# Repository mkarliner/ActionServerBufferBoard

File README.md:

This is a design for a board to buffer the outputs of a Raspberr Pi so that it can drive 5V devices which use up to 500ma. The buffer chips are ULN2003's which are Darlington pair arrays with open collector outputs. This means that they form low side switches. There are many articles on Google for using ULN2003's so I won't detail wiring here. The silkscreen is marked for the connections for the Camerabotics Lensmaster ActionServer to make it easier to wire up.

PLEASE NOTE: This is a first version of this design. I'm working on a second revision with more/easier connections and push/pull outputs. However, you are welcome to use this if you find it useful.

I've included pictures of the assembled board and my initial installation. The installation has three relay outputs and three 240V solid state relays. (The relay board has 8 relays of which one three are used)

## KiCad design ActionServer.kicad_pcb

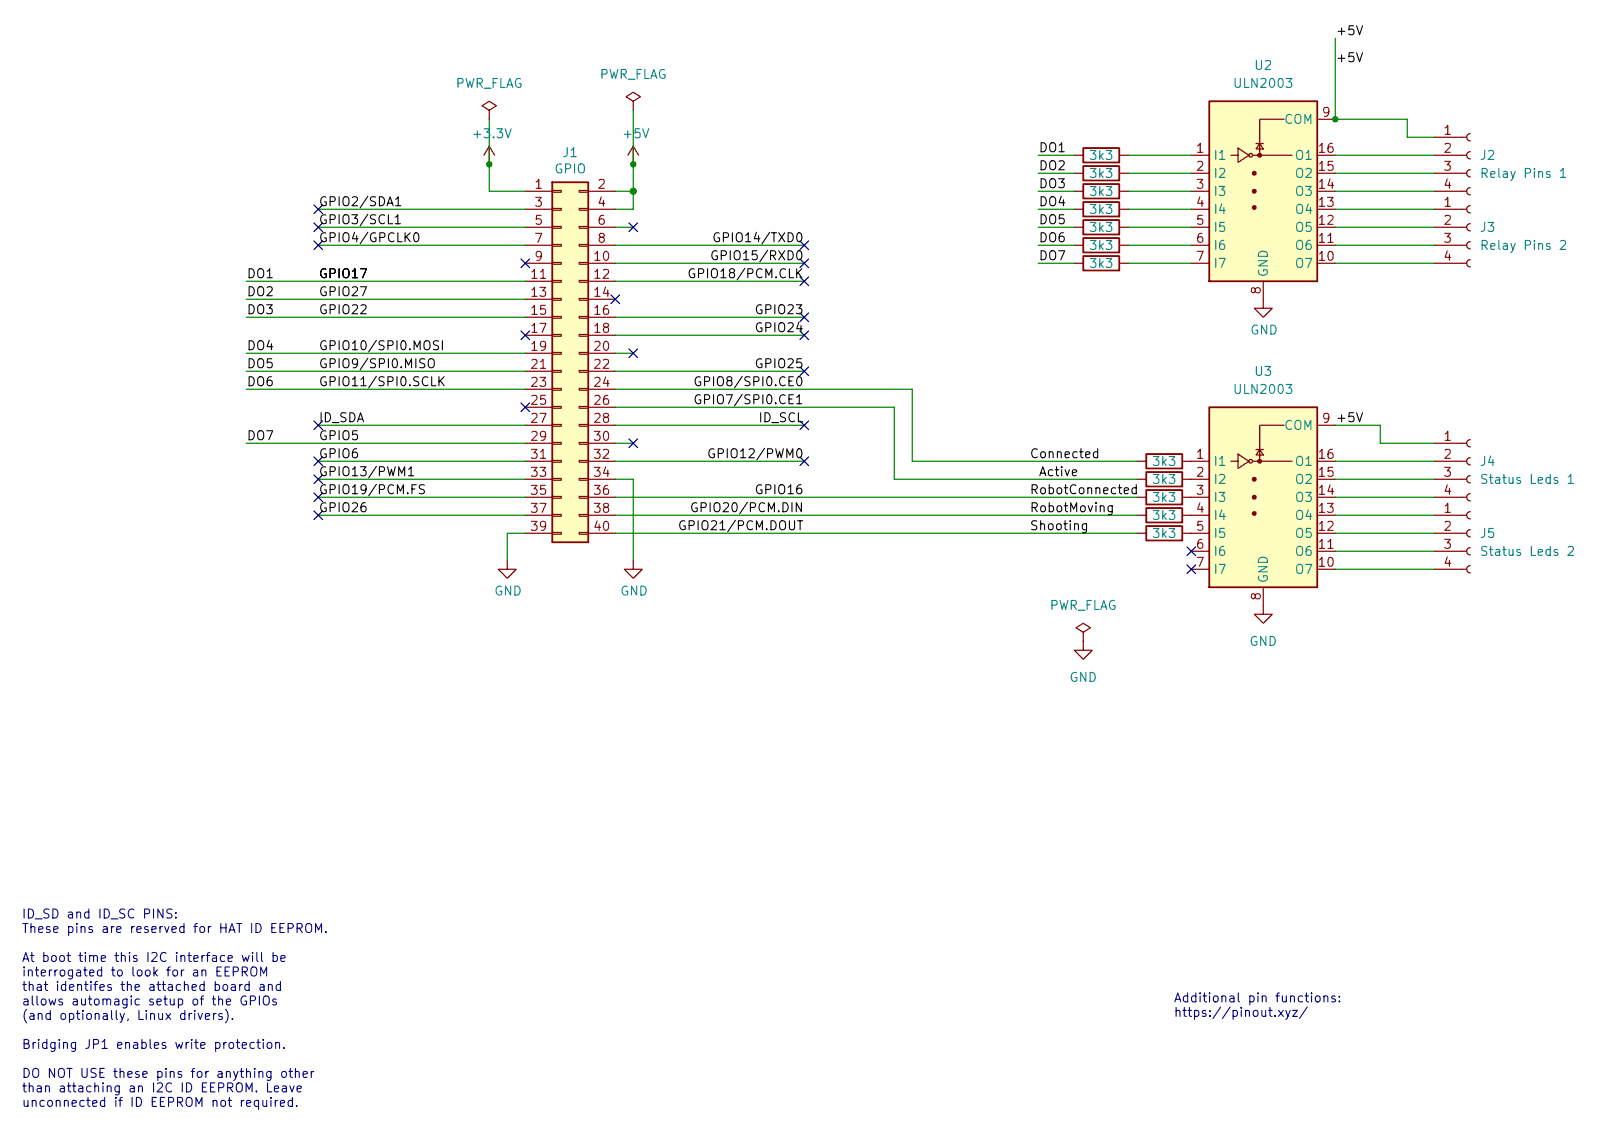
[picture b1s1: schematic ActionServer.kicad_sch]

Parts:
J1: GPIO; PinSocket_2x20_P2.54mm_Vertical
J2: Relay Pins 1; PinHeader_1x04_P2.54mm_Vertical
J3: Relay Pins 2; PinHeader_1x04_P2.54mm_Vertical
J4: Status Leds 1; PinHeader_1x04_P2.54mm_Vertical
J5: Status Leds 2; PinHeader_1x04_P2.54mm_Vertical
R3, R4, R5, R6, R7, R8, R9, R10, R11, R12, R13, R14: 3k3; R_0805_2012Metric
U2, U3: ULN2003; SOIC-16_3.9x9.9mm_P1.27mm

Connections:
+3.3V: J1.1
+5V: J1.2, J1.4, J2.1, J4.1, U2.9 (COM), U3.9 (COM)
/Active: J1.26, R11.1
/Connected: J1.24, R10.1
/DO1: J1.11, R3.1
/DO2: J1.13, R4.1
/DO3: J1.15, R5.1
/DO4: J1.19, R6.1
/DO5: J1.21, R7.1
/DO6: J1.23, R8.1
/DO7: J1.29, R9.1
/GPIO2/SDA1: J1.3
/GPIO3/SCL1: J1.5
/GPIO4/GPCLK0: J1.7
/GPIO6: J1.31
/GPIO12/PWM0: J1.32
/GPIO13/PWM1: J1.33
/GPIO14/TXD0: J1.8
/GPIO15/RXD0: J1.10
/GPIO16: J1.36, R12.1
/GPIO18/PCM.CLK: J1.12
/GPIO19/PCM.FS: J1.35
/GPIO20/PCM.DIN: J1.38, R13.1
/GPIO21/PCM.DOUT: J1.40, R14.1
/GPIO23: J1.16
/GPIO24: J1.18
/GPIO25: J1.22
/GPIO26: J1.37
/ID_SCL: J1.28
/ID_SDA: J1.27
GND: J1.34, J1.39, U2.8 (GND), U3.8 (GND)
unnamed: J2.2, U2.16 (O1)
unnamed: J2.3, U2.15 (O2)
unnamed: J2.4, U2.14 (O3)
unnamed: J3.1, U2.13 (O4)
unnamed: J3.2, U2.12 (O5)
unnamed: J3.3, U2.11 (O6)
unnamed: J3.4, U2.10 (O7)
unnamed: J4.2, U3.16 (O1)
unnamed: J4.3, U3.15 (O2)
unnamed: J4.4, U3.14 (O3)
unnamed: J5.1, U3.13 (O4)
unnamed: J5.2, U3.12 (O5)
unnamed: J5.3, U3.11 (O6)
unnamed: J5.4, U3.10 (O7)
unnamed: R3.2, U2.1 (I1)
unnamed: R4.2, U2.2 (I2)
unnamed: R5.2, U2.3 (I3)
unnamed: R6.2, U2.4 (I4)
unnamed: R7.2, U2.5 (I5)
unnamed: R8.2, U2.6 (I6)
unnamed: R9.2, U2.7 (I7)
unnamed: R10.2, U3.1 (I1)
unnamed: R11.2, U3.2 (I2)
unnamed: R12.2, U3.3 (I3)
unnamed: R13.2, U3.4 (I4)
unnamed: R14.2, U3.5 (I5)

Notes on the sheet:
Additional pin functions: https://pinout.xyz/
ID_SD and ID_SC PINS: These pins are reserved for HAT ID EEPROM. At boot time this I2C interface will be interrogated to look for an EEPROM that identifes the attached board and allows automagic setup of the GPIOs (and optionally, Linux drivers). Bridging JP1 enables write protection. DO NOT USE th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

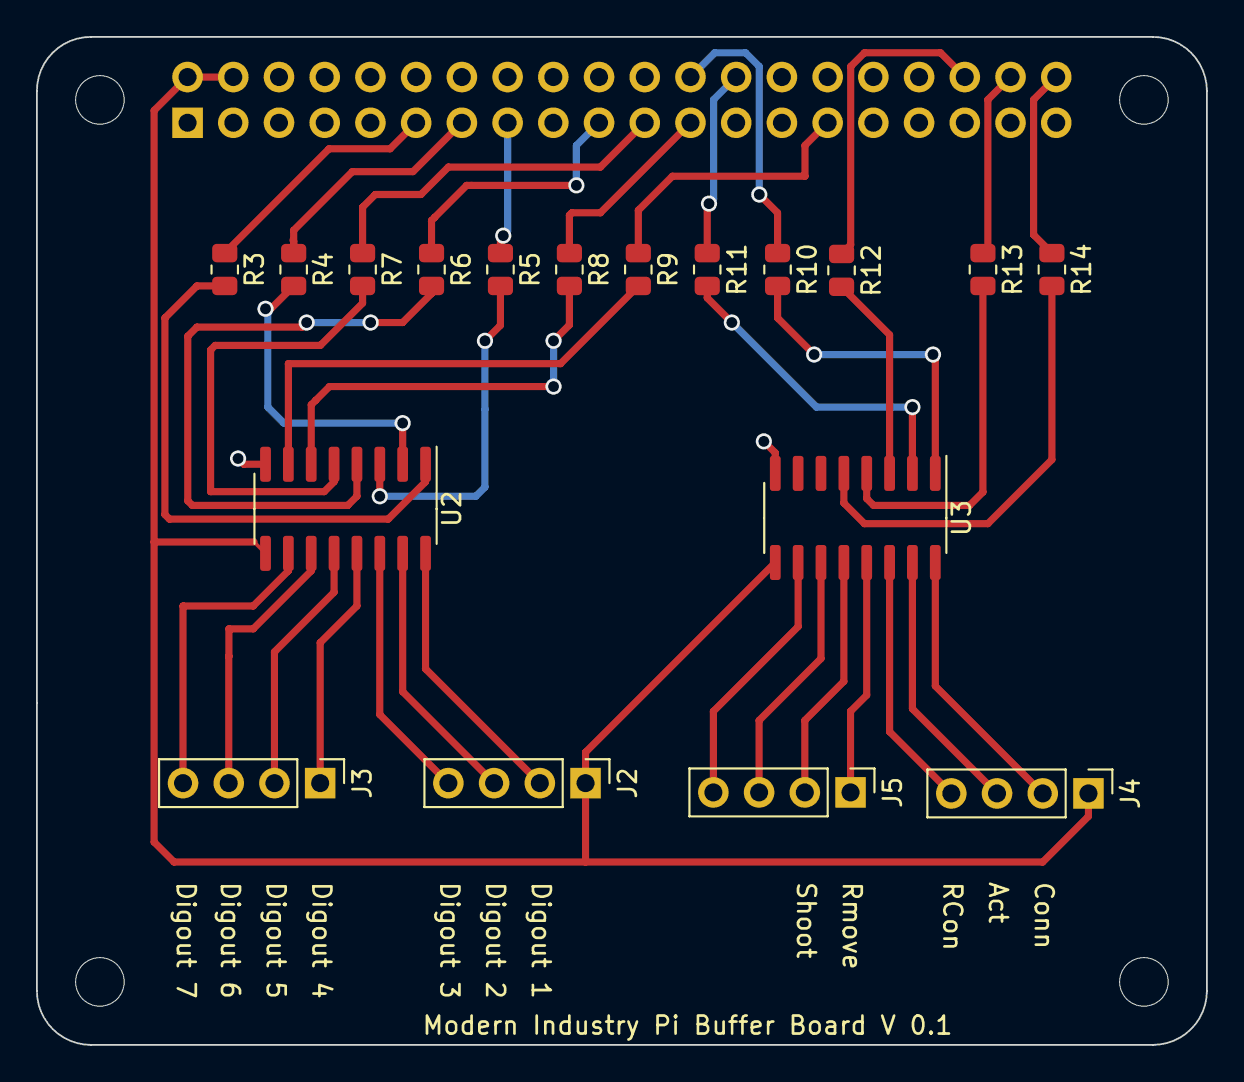
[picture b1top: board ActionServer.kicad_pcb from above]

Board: 2 copper layers, 65.0 x 56.0 mm, 23 parts (1 on the bottom side), 40 nets.

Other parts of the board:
MH1, MH2, MH3, MH4: MountingHole_2.7mm_M2.5

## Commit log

2023-11-16 NEW: First check in
2023-11-16 CHANGE: Add plots folder
2023-11-16 FIX: Output plot options
2024-02-23 Add files via upload
    Pictures of assembled and installed board
2024-02-23 Update README.md
    Picture description
